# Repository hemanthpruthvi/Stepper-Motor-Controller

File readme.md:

# Generic Stepper Motor Controller for Multi-Axis Motion
The project describes a simple and complete solution to multi-axis motion control using generic stepper-motor based mounts with off-the-shelf motor drives, a system that looks like the following.  

Motion controller &rarr; Stepper motor drive &rarr; Motorized rotation/translation stage

The motion controller has two aspects:  
1. Hardware: design files for dsPIC micro-controller based custom board
2. Firmware: embedded-C program that implements the motion controls

## Hardware
The central element is a dsPIC micro-controller with two UART ports and several I/O ports that enable control of upto 3 drives at a time by sending correspinding pulse trains (drive IDs 1-3). Up to three of such motion controllers can be connected in daisy chain thus being able to control upto nine drives (drive IDs 1-9). The number of daisy chains is only a firmware limitation due to how the drives are numbered. A better numbering scheme should allow for more expansion.

The directory `Hardware` contains the design files. Hardware circuitry is designed using `KiCAD` program. The final `GERBER` file should be enough to produce the custom printed circuit boards.

## Firmware
The firmware is programmed in Embedded-C using `MPLABX IDE` with a header that is specific to the micro-controller of choice. The directory `Firmware` contains the source code as well as the compiled output. The firmware is written into the hardware using `PIKIT 3` programmer tool. The `HEX` file to be written to hardware is located at`<firmware directory>/dist/default/Production`.

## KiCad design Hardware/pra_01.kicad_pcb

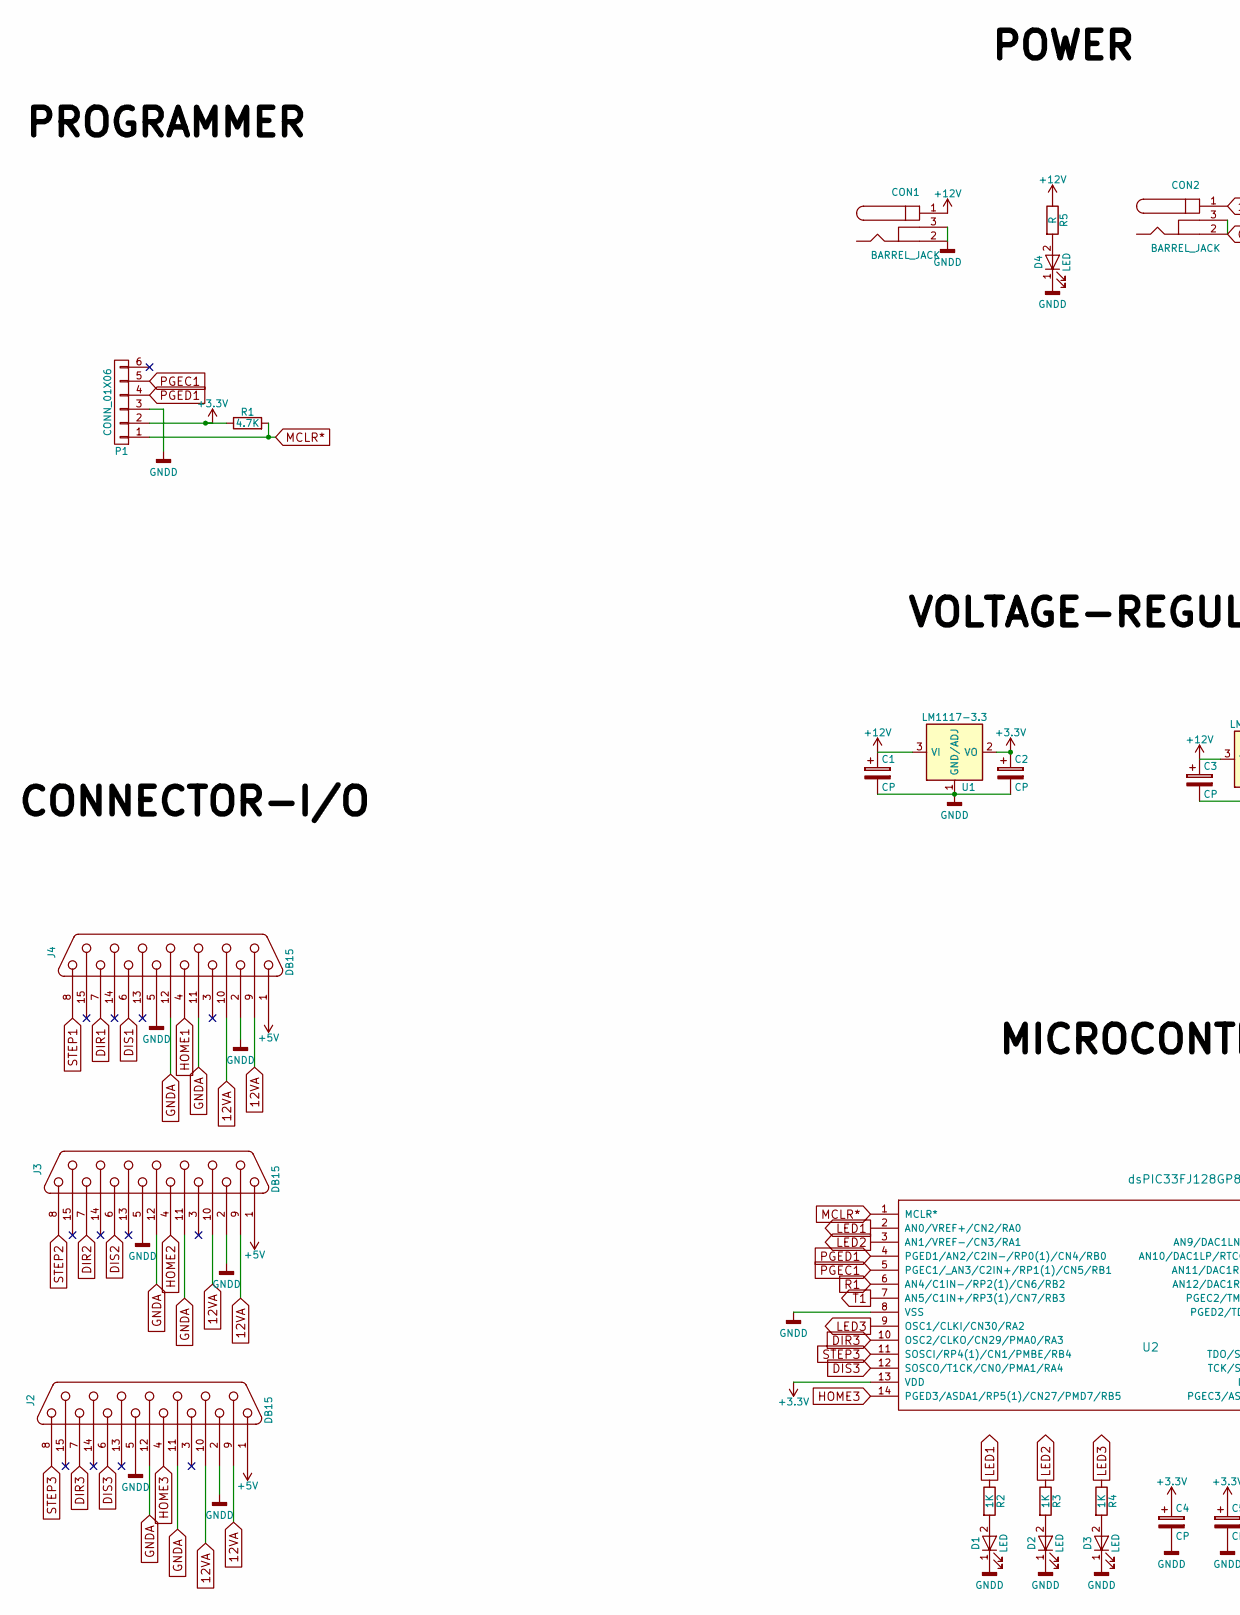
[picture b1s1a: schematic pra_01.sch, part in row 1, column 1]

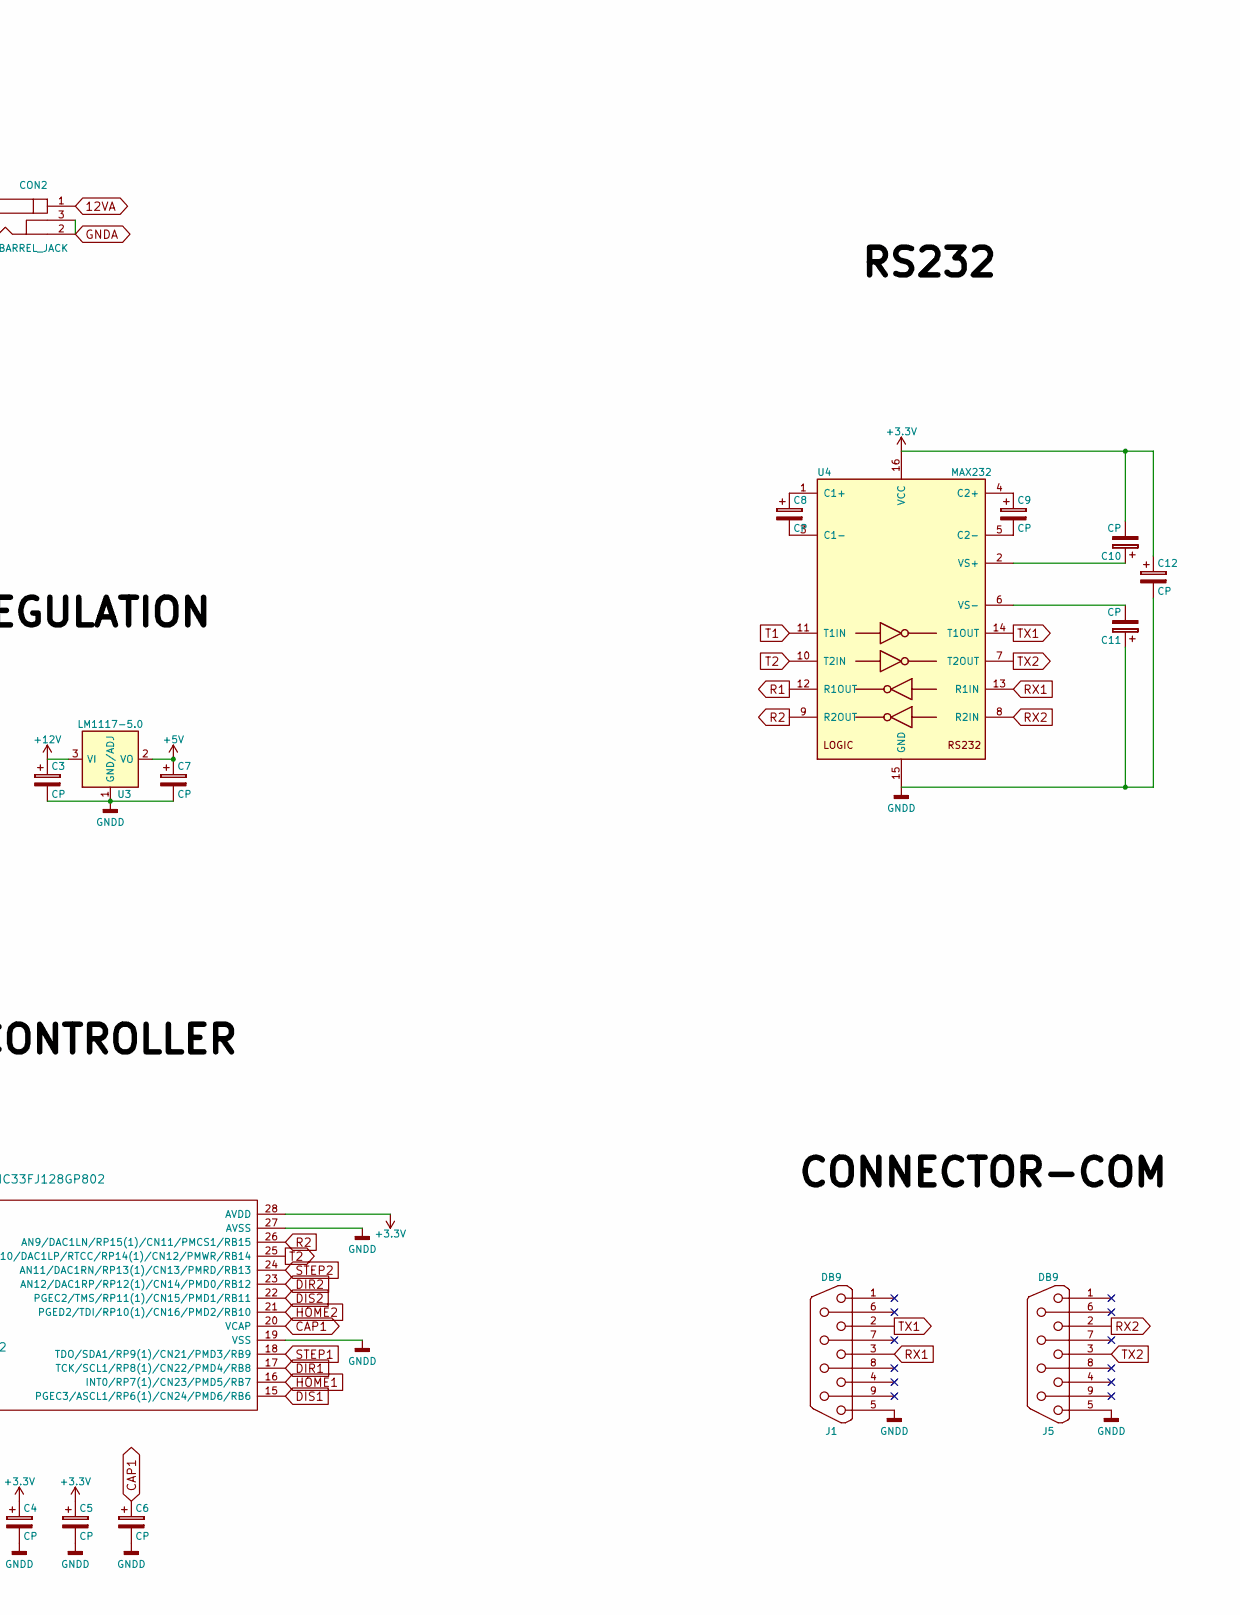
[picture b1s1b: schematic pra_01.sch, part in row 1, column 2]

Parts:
C1, C2, C3, C6, C7: CP; CP_Radial_D5.0mm_P2.50mm
C4, C5, C8, C9, C10, C11, C12: CP; CP_Radial_Tantal_D5.0mm_P2.50mm
CON1, CON2: BARREL_JACK
D1, D2, D3: LED; LED_1206
D4: LED; LED_D5.0mm
J1: DB9; DB9FC
J2, J3, J4: DB15; DB15FC
J5: DB9; DB9MC
P1: CONN_01X06; PINHEAD1-6
R1: 4.7K; R_1206_HandSoldering
R2, R3, R4: 1K; R_1206_HandSoldering
R5: R; Resistor_SMD+THTuniversal_0805to1206_RM10_HandSoldering
U1: LM1117-3.3; TO-220
U2: dsPIC33FJ128GP802; DIP-28_W7.62mm
U3: LM1117-5.0; TO-220
U4: MAX232; DIP-16_W7.62mm_LongPads

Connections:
12VA: CON2.1, J2.9, J2.10, J3.9, J3.10, J4.9, J4.10
+3V3: C2.1, C4.1, C5.1, C10.2, C12.1, P1.2, R1.1, U1.2 (VO), U1.4 (VO), U2.13 (VDD), U2.28 (AVDD), U4.16 (VCC)
+5V: C7.1, J2.1, J3.1, J4.1, U3.2 (VO), U3.4 (VO)
+12V: C1.1, C3.1, CON1.1, R5.1, U1.3 (VI), U3.3 (VI)
CAP1: C6.1, U2.20 (VCAP)
DIR1: J4.7, U2.17 (TCK/SCL1/RP8(1)/CN22/PMD4/RB8)
DIR2: J3.7, U2.23 (AN12/DAC1RP/RP12(1)/CN14/PMD0/RB12)
DIR3: J2.7, U2.10 (OSC2/CLKO/CN29/PMA0/RA3)
DIS1: J4.6, U2.15 (PGEC3/ASCL1/RP6(1)/CN24/PMD6/RB6)
DIS2: J3.6, U2.22 (PGEC2/TMS/RP11(1)/CN15/PMD1/RB11)
DIS3: J2.6, U2.12 (SOSCO/T1CK/CN0/PMA1/RA4)
GNDA: CON2.2, CON2.3, J2.11 (P111), J2.12, J3.11 (P111), J3.12, J4.11 (P111), J4.12
GNDD: C1.2, C2.2, C3.2, C4.2, C5.2, C6.2, C7.2, C11.1, C12.2, CON1.2, CON1.3, D1.1 (K), D2.1 (K), D3.1 (K), D4.1 (K), J1.5, J2.2, J2.5, J3.2, J3.5, J4.2, J4.5, J5.5, P1.3, U1.1 (GND/ADJ), U2.8 (VSS), U2.19 (VSS), U2.27 (AVSS), U3.1 (GND/ADJ), U4.15 (GND)
HOME1: J4.4, U2.16 (INT0/RP7(1)/CN23/PMD5/RB7)
HOME2: J3.4, U2.21 (PGED2/TDI/RP10(1)/CN16/PMD2/RB10)
HOME3: J2.4, U2.14 (PGED3/ASDA1/RP5(1)/CN27/PMD7/RB5)
LED1: R2.1, U2.2 (AN0/VREF+/CN2/RA0)
LED2: R3.1, U2.3 (AN1/VREF-/CN3/RA1)
LED3: R4.1, U2.9 (OSC1/CLKI/CN30/RA2)
MCLR*: P1.1, R1.2, U2.1 (MCLR*)
unnamed: C8.1, U4.1 (C1+)
unnamed: C8.2, U4.3 (C1-)
unnamed: C9.1, U4.4 (C2+)
unnamed: C9.2, U4.5 (C2-)
unnamed: C10.1, U4.2 (VS+)
unnamed: C11.2, U4.6 (VS-)
unnamed: D1.2 (A), R2.2
unnamed: D2.2 (A), R3.2
unnamed: D3.2 (A), R4.2
unnamed: D4.2 (A), R5.2
PGEC1: P1.5, U2.5 (PGEC1/_AN3/C2IN+/RP1(1)/CN5/RB1)
PGED1: P1.4, U2.4 (PGED1/AN2/C2IN-/RP0(1)/CN4/RB0)
R1: U2.6 (AN4/C1IN-/RP2(1)/CN6/RB2), U4.12 (R1OUT)
R2: U2.26 (AN9/DAC1LN/RP15(1)/CN11/PMCS1/RB15), U4.9 (R2OUT)
RX1: J1.3, U4.13 (R1IN)
RX2: J5.2, U4.8 (R2IN)
STEP1: J4.8, U2.18 (TDO/SDA1/RP9(1)/CN21/PMD3/RB9)
STEP2: J3.8, U2.24 (AN11/DAC1RN/RP13(1)/CN13/PMRD/RB13)
STEP3: J2.8, U2.11 (SOSCI/RP4(1)/CN1/PMBE/RB4)
T1: U2.7 (AN5/C1IN+/RP3(1)/CN7/RB3), U4.11 (T1IN)
T2: U2.25 (AN10/DAC1LP/RTCC/RP14(1)/CN12/PMWR/RB14), U4.10 (T2IN)
TX1: J1.2, U4.14 (T1OUT)
TX2: J5.3, U4.7 (T2OUT)

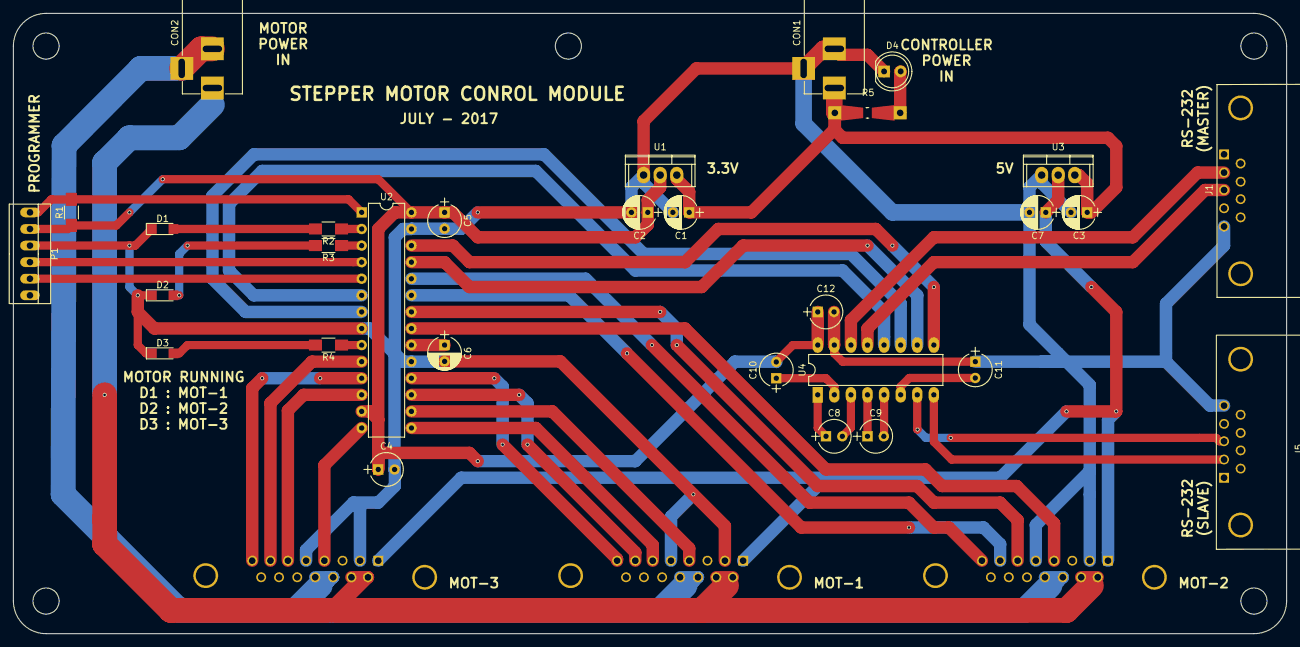
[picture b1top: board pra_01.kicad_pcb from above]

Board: 2 copper layers, 195.0 x 95.0 mm, 33 parts (0 on the bottom side), 43 nets.

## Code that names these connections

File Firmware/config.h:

/* 
 * File:   
 * Author: 
 * Comments:
 * Revision history: 
 */ 
#ifndef XC_CONFIG_H
    #define	XC_CONFIG_H
    #include <xc.h> // include processor files - each processor file is guarded
    #include <p33FJ128GP802.h>

// Define required parameters
    // Internal oscillator
    #define FOSC (80000000) // Oscillator frequency (approx.)(To be set)
    #define FCY (FOSC/2)    // Peripheral clock frequency (To be set
    // Timers
    #define TIMER_VAL(FREQ) ((FCY/64)/2)/FREQ) // To be given by user
    // UARTs
    #define BAUDRATE1 (115200)
    #define WAIT_TX1 (FCY/BAUDRATE1)
    #define BRGVAL1 (((FCY/BAUDRATE1)/16)-1) 
    #define BAUDRATE2 (115200)
    #define WAIT_TX2 (FCY/BAUDRATE2)
    #define BRGVAL2 (((FCY/BAUDRATE2)/16)-1) 
    // LEDs
    #define LED1 LATAbits.LATA0
    #define LED2 LATAbits.LATA1
    #define LED3 LATAbits.LATA2
    // Motor-1 controls
    #define STEP1 LATBbits.LATB9
    #define DIR1 LATBbits.LATB8
    #define DIS1 LATBbits.LATB6 
    // Motor-2 controls
    #define STEP2 LATBbits.LATB13
    #define DIR2 LATBbits.LATB12
    #define DIS2 LATBbits.LATB11
    // Motor-3 controls
    #define STEP3 LATBbits.LATB4
    #define DIR3 LATAbits.LATA3
    #define DIS3 LATAbits.LATA4

// Define initialization functions for modules
    // Initialize Oscillator
    void INIT_OSCLI(void);    
    // Initialize timers
    void INIT_TIMR2(void);    
    void INIT_TIMR3(void);
    void INIT_TIMR4(void);
    // Initialize UARTs
    void INIT_UART1(void);
    void INIT_UART2(void);
    // Initialize I/O pins
    void INIT_INOUT(void);
    // Initialize External interrupts
    void INIT_INTRR(void);
    
    //  Define custom functions
    void U1TX_SENDCHR(unsigned char);
    void U1TX_SENDSTR(unsigned char *);
    void U2TX_SENDCHR(unsigned char);
    void U2TX_SENDSTR(unsigned char *);
    
// Define commonly used symbols here
    #define FIRST_CHAR '<'  // Command's first character
    #define LAST_CHAR '>'   // Command's last character
    #define YES 1
    #define NO 0
    #define ON 1
    #define OFF 0

// Declare global variables
    extern unsigned char COMMAND[16];   // Command array
    extern unsigned char SLAVE_COMMAND[16]; // Command array for slave
    extern unsigned int COMM_IND;       // Command array index
    extern unsigned int COMM_LEN;       // Command length
    extern unsigned int COMM_REC;       // Command received?
    extern unsigned char SRESPONSE[4];   // Slave Response for the commands, 3rd char is always '\n'
    extern unsigned char MRESPONSE[4];   // Master Response for the commands, 3rd char is always '\n'
    
    extern unsigned int NUMBER_MOTO;    // Motor number
    extern unsigned int FUNCTION_MOTO;  // Function of drivers
    extern unsigned long int NUMBER;         // Numerical value
    
    extern unsigned int MOT1_ROTAT; // Motor-1 rotation?
    extern unsigned int MOT1_HOME;  // Motor-1 homing?
    extern unsigned long int STEP1_NUM;  // Number of steps left
    extern unsigned long int HSTEP1_NUM; // Number of toggles (half-steps)  = 2* Number of steps
    extern unsigned int STEP1_FREQ; // Step frequency
    extern unsigned long int POS1_CURRENT; // Current value - 1
   
    extern unsigned int MOT2_ROTAT; // Motor-2 rotation?
    extern unsigned int MOT2_HOME;  // Motor-2 homing?
    extern unsigned long int STEP2_NUM;  // Number of steps left
    extern unsigned long int HSTEP2_NUM; // Number of toggles (half-steps) = 2* Number of steps
    extern unsigned int STEP2_FREQ; // Step frequency
    extern unsigned long int POS2_CURRENT; // Current value - 2

    
    extern unsigned int MOT3_ROTAT; // Motor-3 rotation?
    extern unsigned int MOT3_HOME;  // Motor-3 homing?
    extern unsigned long int STEP3_NUM;  // Number of steps left
    extern unsigned long int HSTEP3_NUM; // Number of toggles (half-steps) = 2* Number of steps
    extern unsigned int STEP3_FREQ; // Step frequency
    extern unsigned long int POS3_CURRENT; // Current value - 3
#endif	/* XC_CONFIG_H */

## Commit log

2025-03-18 Github upload
2025-03-18 readme edit
